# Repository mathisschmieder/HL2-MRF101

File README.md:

100W Amplifier Companion for the Hermes-Lite 2.x
================================================

See the [Wiki](https://github.com/mathisschmieder/HL2-MRF101/wiki) for details.

This is a work in progress to create a 100W power amplifier companion board for the [Hermes-Lite 2.x](http://www.hermeslite.com) using the NXP MRF101 MOSFET. It is based on WA2EUJ's [Single NXP MRF-101 Eval Board](https://sites.google.com/site/rfpowertools/) that won 1st place in the NXP Design Challenge.

First builds of revision 0.2 are successful. Several changes and additions were done by M5EVT to revision 0.3 and boards of that revision are currently being built and tested. See the Wiki for further links and details.

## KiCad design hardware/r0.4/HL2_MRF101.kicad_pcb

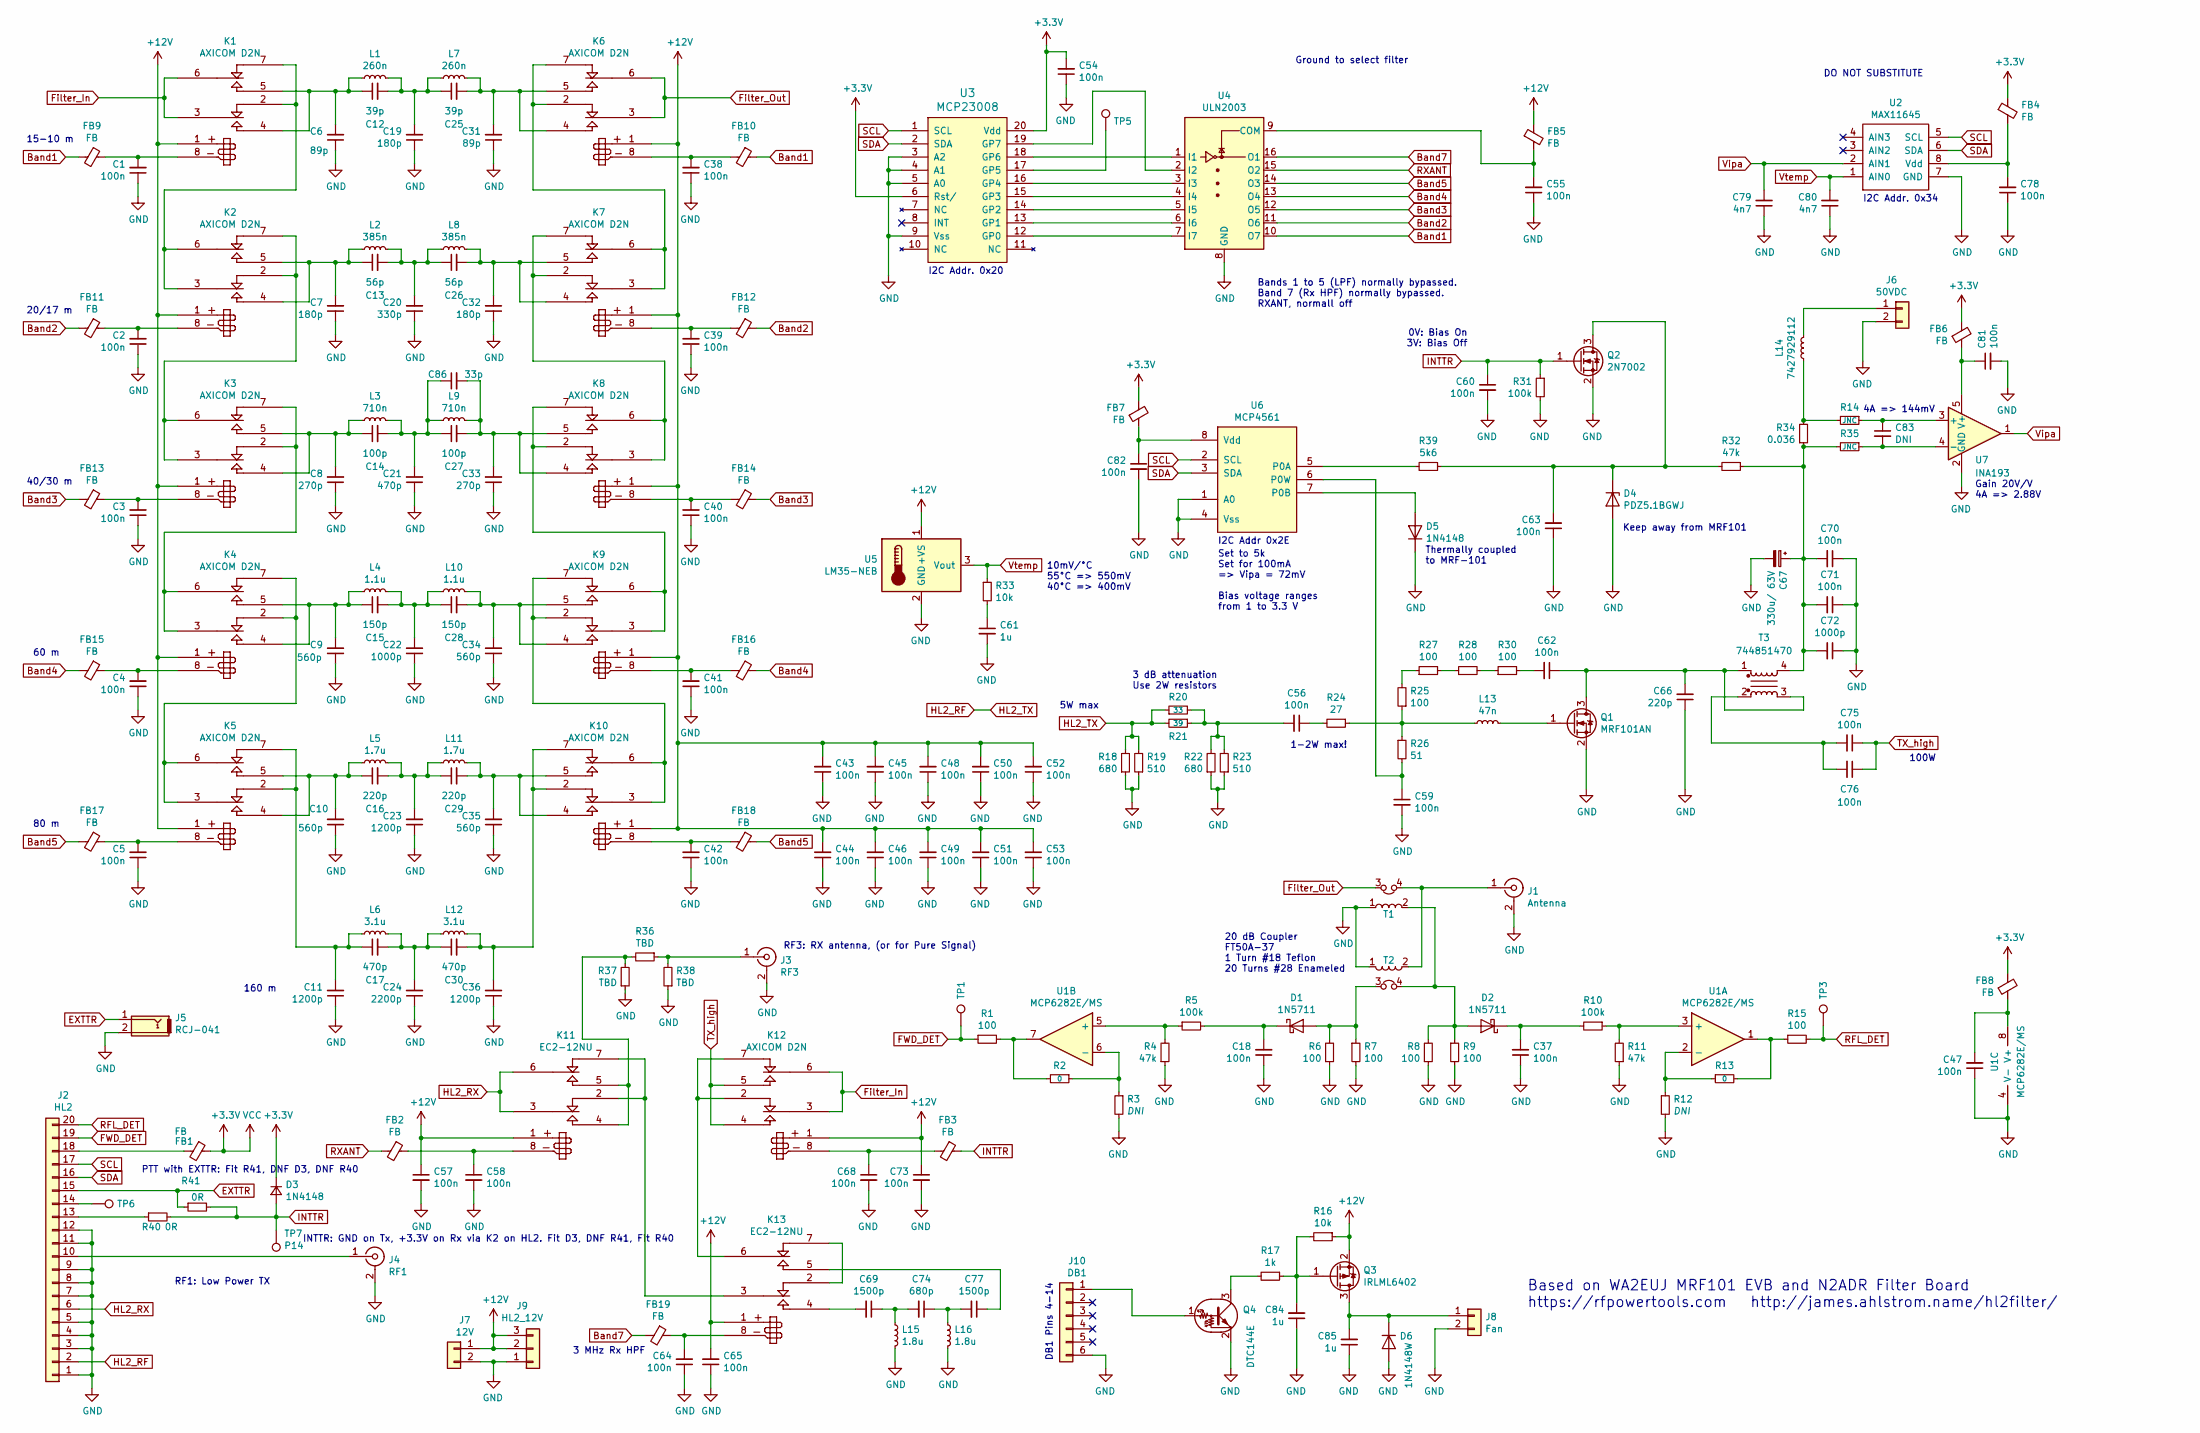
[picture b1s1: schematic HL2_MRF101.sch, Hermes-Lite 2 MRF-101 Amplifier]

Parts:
C1, C2, C3, C4, C5, C18, C37, C38, C39, C40, C41, C42, C43, C44, C45, C46, C47, C48, C49, C50, C51, C52, C53, C54, C55, C56, C57, C58, C59, C60, C62, C63, C64, C65, C68, C70, C71, C73, C75, C76, C78, C81, C82: 100n; C_0805_2012Metric
C6, C31: 89p; C_1206_3216Metric
C7, C19, C32: 180p; C_1206_3216Metric
C8, C33: 270p; C_1206_3216Metric
C9, C10, C34, C35: 560p; C_1206_3216Metric
C11, C23, C36: 1200p; C_1206_3216Metric
C12, C25: 39p; C_1206_3216Metric
C13, C26: 56p; C_1206_3216Metric
C14, C27: 100p; C_1206_3216Metric
C15, C28: 150p; C_1206_3216Metric
C16, C29: 220p; C_1206_3216Metric
C17, C21, C30: 470p; C_1206_3216Metric
C20: 330p; C_1206_3216Metric
C22: 1000p; C_1206_3216Metric
C24: 2200p; C_1206_3216Metric
C61, C84, C85: 1u; C_0805_2012Metric
C66: 220p; C_0805_2012Metric
C67: 330u/ 63V; CP_Radial_D10.0mm_P5.00mm
C69, C77: 1500p; C_0805_2012Metric
C72: 1000p; C_0805_2012Metric
C74: 680p; C_0805_2012Metric
C79, C80: 4n7; C_0805_2012Metric
C83: DNI; C_0805_2012Metric
C86: 33p; C_1206_3216Metric
D1, D2: 1N5711; D_SOD-123
D3: 1N4148; D_SOD-123
D4: PDZ5.1BGWJ; D_SOD-123
D5: 1N4148; D_DO-35_SOD27_P2.54mm_Vertical_KathodeUp
D6: 1N4148W; D_SOD-123
FB1, FB2, FB3, FB4, FB5, FB6, FB7, FB8, FB9, FB10, FB11, FB12, FB13, FB14, FB15, FB16, FB17, FB18, FB19: FB; L_0805_2012Metric
J1: Antenna; BNC_Amphenol_B6252HB-NPP3G-50_Horizontal
J2: HL2; PinSocket_1x20_P2.54mm_Vertical
J3: RF3; U.FL_Hirose_U.FL-R-SMT-1_Vertical
J4: RF1; U.FL_Hirose_U.FL-R-SMT-1_Vertical
J5: RCJ-041; PhonoRcaRCJ-04x
J6: 50VDC; TerminalBlock_Phoenix_PT-1,5-2-5.0-H_1x02_P5.00mm_Horizontal
J7: 12V; TerminalBlock_Phoenix_PT-1,5-2-3.5-H_1x02_P3.50mm_Horizontal
J8: Fan; JST_XH_B2B-XH-A_1x02_P2.50mm_Vertical
J9: HL2_12V; PinSocket_1x03_P2.54mm_Vertical
J10: DB1; PinHeader_1x06_P2.54mm_Vertical
K1, K2, K3, K4, K5, K6, K7, K8, K9, K10, K12: AXICOM D2N; RelayDPDT02
K11, K13: EC2-12NU; RelayDPDT01
L1, L7: 260n; T50_V_THT
L2, L8: 385n; T50_V_THT
L3, L9: 710n; T50_V_THT
L4, L10: 1.1u; T50_V_THT
L5, L11: 1.7u; T50_V_THT
L6, L12: 3.1u; T50_V_THT
L13: 47n; L_0805_2012Metric
L14: 7427929112; SignalCommunications-WE-PF_7427929XXX
L15, L16: 1.8u; L_1812_4532Metric
Q1: MRF101AN; TO-220-3_Vertical
Q2: 2N7002; SOT-23
Q3: IRLML6402; SOT-23
Q4: DTC144E; SOT-23
R1, R15: 100; R_0805_2012Metric
R2, R13: 0; R_0805_2012Metric
R3, R12: DNI; R_0805_2012Metric
R4, R11, R32: 47k; R_0805_2012Metric
R5, R10, R31: 100k; R_0805_2012Metric
R6, R7, R8, R9, R25, R27, R28, R30: 100; R_2512_6332Metric
R14, R35: JNC; R_0805_2012Metric
R16, R33: 10k; R_0805_2012Metric
R17: 1k; R_0805_2012Metric
R18, R22: 680; R_2512_6332Metric
R19, R23: 510; R_2512_6332Metric
R20: 33; R_2512_6332Metric
R21: 39; R_2512_6332Metric
R24: 27; R_2512_6332Metric
R26: 51; R_2512_6332Metric
R34: 0.036; R_0612_1632Metric
R36, R37, R38: TBD; R_0805_2012Metric
R39: 5k6; R_0805_2012Metric
R40, R41: 0R; R_0603_1608Metric
T1, T2: Coupler; T50_Coupler
T3: 744851470; SignalCommunications-WE-DCT
TP1, TP3, TP5, TP6: P8; TestPoint_Pad_D1.5mm
TP7: P14; TestPoint_Pad_D1.5mm
U1: MCP6282E/MS; MSOP-8_3x3mm_P0.65mm
U2: MAX11645; MAX11613
U3: MCP23008; SSOP-20_5.3x7.2mm_P0.65mm
U4: ULN2003; TSSOP-16_4.4x5mm_P0.65mm
U5: LM35-NEB; TO-220-3_Vertical
U6: MCP4561; MSOP-8_3x3mm_P0.65mm
U7: INA193; SOT-23-5

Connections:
+3V3: C54.2, D3.1 (K), FB1.1, FB4.1, FB6.2, FB7.2, FB8.2, U3.6 (Rst/), U3.20 (Vdd)
+12V: C43.2, C44.2, C45.2, C46.2, C48.2, C49.2, C50.2, C51.2, C52.2, C53.2, C57.1, C65.2, C73.1, FB5.1, J7.1, J9.2, J9.3, K1.1, K2.1, K3.1, K4.1, K5.1, K6.1, K7.1, K8.1, K9.1, K10.1, K11.1, K12.1, K13.1, Q3.2 (S), R16.1, U5.1 (+VS)
Band1: FB9.2, FB10.1, U4.10 (O7)
Band2: FB11.2, FB12.1, U4.11 (O6)
Band3: FB13.2, FB14.1, U4.12 (O5)
Band4: FB15.2, FB16.1, U4.13 (O4)
Band5: FB17.2, FB18.1, U4.14 (O3)
Band7: FB19.2, U4.16 (O1)
EXTTR: J2.15, J5.1, R41.1
FWD_DET: J2.19, R1.1, TP1.1
Filter_In: K1.3, K1.6, K12.3, K12.6
Filter_Out: K6.3, K6.6, T1.3
GND: C1.1, C2.1, C3.1, C4.1, C5.1, C6.1, C7.1, C8.1, C9.1, C10.1, C11.1, C18.1, C19.1, C20.1, C21.1, C22.1, C23.1, C24.1, C31.1, C32.1, C33.1, C34.1, C35.1, C36.1, C37.1, C38.1, C39.1, C40.1, C41.1, C42.1, C43.1, C44.1, C45.1, C46.1, C47.1, C48.1, C49.1, C50.1, C51.1, C52.1, C53.1, C54.1, C55.1, C57.2, C58.2, C59.2, C60.2, C61.2, C63.1, C64.1, C65.1, C66.1, C67.2, C68.2, C70.1, C71.1, C72.1, C73.2, C78.1, C79.1, C80.1, C81.2, C82.2, C84.1, C85.1, D4.2 (A), D5.1 (K), D6.2 (A), J1.2 (Ext), J2.1, J2.3, J2.4, J2.5, J2.7, J2.8, J2.9, J2.11, J2.12, J3.2 (Ext), J4.2 (Ext), J5.2, J6.2, J7.2, J8.2, J9.1, J10.6, L15.2, L16.2, Q1.2 (S), Q2.2 (S), Q4.2 (E), R3.2, R4.1, R6.1, R7.2, R8.1, R9.2, R11.1, R12.2, R18.1, R19.1, R22.1, R23.1, R31.2, R37.1, R38.1, T1.1, T2.1, U1.4 (V-), U2.7 (GND), U3.3 (A2), U3.4 (A1), U3.5 (A0), U3.9 (Vss), U4.8 (GND), U5.2 (GND), U6.1 (A0), U6.4 (Vss), U7.2 (GND); also elsewhere on the board
HL2_RF: J2.2, R18.2, R19.2, R20.1, R21.2
HL2_RX: J2.6, K11.3, K11.6
INTTR: C60.1, D3.2 (A), FB3.1, Q2.1 (G), R31.1, R40.2, R41.2, TP7.1
unnamed: C1.2, FB9.1, K1.8
unnamed: C2.2, FB11.1, K2.8
unnamed: C3.2, FB13.1, K3.8
unnamed: C4.2, FB15.1, K4.8
unnamed: C5.2, FB17.1, K5.8
unnamed: C10.2, C16.1, K5.4, K5.5, L5.1
unnamed: C11.2, C17.1, K5.2, K5.7, L6.1
unnamed: C6.2, C12.1, K1.4, K1.5, L1.1
unnamed: C12.2, C19.2, C25.1, L1.2, L7.1
unnamed: C7.2, C13.1, K2.4, K2.5, L2.1
unnamed: C13.2, C20.2, C26.1, L2.2, L8.1
unnamed: C8.2, C14.1, K3.4, K3.5, L3.1
unnamed: C14.2, C21.2, C27.1, C86.1, L3.2, L9.1
unnamed: C9.2, C15.1, K4.4, K4.5, L4.1
unnamed: C15.2, C22.2, C28.1, L4.2, L10.1
unnamed: C16.2, C23.2, C29.1, L5.2, L11.1
unnamed: C17.2, C24.2, C30.1, L6.2, L12.1
unnamed: C18.2, D1.1 (K), R5.2
unnamed: C25.2, C31.2, K6.4, K6.5, L7.2
unnamed: C26.2, C32.2, K7.4, K7.5, L8.2
unnamed: C27.2, C33.2, C86.2, K8.4, K8.5, L9.2
unnamed: C28.2, C34.2, K9.4, K9.5, L10.2
unnamed: C29.2, C35.2, K10.4, K10.5, L11.2
unnamed: C30.2, C36.2, K10.2, K10.7, L12.2
unnamed: C37.2, D2.1 (K), R10.2
unnamed: C38.2, FB10.2, K6.8
unnamed: C39.2, FB12.2, K7.8
unnamed: C40.2, FB14.2, K8.8
unnamed: C41.2, FB16.2, K9.8
unnamed: C42.2, FB18.2, K10.8
unnamed: C47.2, FB8.1, U1.8 (V+)
unnamed: C55.2, FB5.2, U4.9 (COM)
unnamed: C56.1, R24.2
unnamed: C56.2, R20.2, R21.1, R22.2, R23.2
unnamed: C58.1, FB2.1, K11.8
unnamed: C59.1, R26.2, U6.6 (P0W)
unnamed: C61.1, R33.2
unnamed: C62.1, C66.2, Q1.3 (D), T3.1, T3.3
unnamed: C62.2, R30.2
unnamed: C63.2, D4.1 (K), Q2.3 (D), R32.2, R39.1
unnamed: C64.2, FB19.1, K13.8
unnamed: C67.1, C70.2, C71.2, C72.2, R32.1, R34.1, R35.2, T3.4
unnamed: C68.1, FB3.2, K12.8
unnamed: C69.1, C74.2, L15.1
unnamed: C69.2, K13.4
unnamed: C74.1, C77.2, L16.1
unnamed: C75.2, C76.2, T3.2
unnamed: C77.1, K13.5
unnamed: C78.2, FB4.2, U2.8 (Vdd)
unnamed: C81.1, FB6.1, U7.5 (V+)
unnamed: C82.1, FB7.1, U6.8 (Vdd)
unnamed: C83.1, R14.1, U7.3 (+)
unnamed: C83.2, R35.1, U7.4 (-)
unnamed: C84.2, Q3.1 (G), R16.2, R17.1
unnamed: C85.2, D6.1 (K), J8.1, Q3.3 (D)
unnamed: D1.2 (A), R6.2, R7.1, T2.3
unnamed: D2.2 (A), R8.2, R9.1, T1.2, T2.4
unnamed: D5.2 (A), U6.7 (P0B)
unnamed: FB1.2, J2.18
unnamed: J1.1 (In), T1.4, T2.2
unnamed: J2.10, J4.1 (In)
unnamed: J2.13, R40.1
unnamed: J2.14, TP6.1
unnamed: J3.1 (In), R36.1, R38.2
unnamed: J6.1, L14.1
unnamed: J10.1, Q4.1 (B)
unnamed: K1.2, K1.7, K2.3, K2.6
unnamed: K2.2, K2.7, K3.3, K3.6
unnamed: K3.2, K3.7, K4.3, K4.6
unnamed: K4.2, K4.7, K5.3, K5.6
unnamed: K6.2, K6.7, K7.3, K7.6
unnamed: K7.2, K7.7, K8.3, K8.6
unnamed: K8.2, K8.7, K9.3, K9.6
unnamed: K9.2, K9.7, K10.3, K10.6
unnamed: K11.2, K11.7, K13.3
unnamed: K11.4, K11.5, R36.2, R37.2
unnamed: K12.2, K12.7, K13.6
unnamed: K13.2, K13.7
unnamed: L13.1, R24.1, R25.1, R26.1
unnamed: L13.2, Q1.1 (G)
unnamed: L14.2, R14.2, R34.2
unnamed: Q4.3 (C), R17.2
unnamed: R1.2, R2.2, U1.7
unnamed: R2.1, R3.1, U1.6 (-)
unnamed: R4.2, R5.1, U1.5 (+)
unnamed: R10.1, R11.2, U1.3 (+)
unnamed: R12.1, R13.1, U1.2 (-)
unnamed: R13.2, R15.1, U1.1
unnamed: R25.2, R27.1
unnamed: R27.2, R28.1
unnamed: R28.2, R30.1
unnamed: R39.2, U6.5 (P0A)
unnamed: TP5.1, U3.17 (GP5)
unnamed: U3.12 (GP0), U4.7 (I7)
unnamed: U3.13 (GP1), U4.6 (I6)
unnamed: U3.14 (GP2), U4.5 (I5)
unnamed: U3.15 (GP3), U4.4 (I4)
unnamed: U3.16 (GP4), U4.3 (I3)
unnamed: U3.18 (GP6), U4.1 (I1)
unnamed: U3.19 (GP7), U4.2 (I2)
RFL_DET: J2.20, R15.2, TP3.1
RXANT: FB2.2, U4.15 (O2)
SCL: J2.17, U2.5 (SCL), U3.1 (SCL), U6.2 (SCL)
SDA: J2.16, U2.6 (SDA), U3.2 (SDA), U6.3 (SDA)
TX_high: C75.1, C76.1, K12.4, K12.5
Vipa: C79.2, U2.2 (AIN1), U7.1
Vtemp: C80.2, R33.1, U2.1 (AIN0), U5.3 (Vout)

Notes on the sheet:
0V: Bias On 3V: Bias Off
Thermally coupled to MRF-101
Set to 5k Set for 100mA => Vipa = 72mV Bias voltage ranges from 1 to 3.3 V
1-2W max!
100W
Based on WA2EUJ MRF101 EVB and N2ADR Filter Board https://rfpowertools.com http://james.ahlstrom.name/hl2filter/
3 dB attenuation Use 2W resistors
20 dB Coupler FT50A-37 1 Turn #18 Teflon 20 Turns #28 Enameled
3 MHz Rx HPF
15-10 m
20/17 m
40/30 m
60 m
80 m
160 m
Bands 1 to 5 (LPF) normally bypassed. Band 7 (Rx HPF) normally bypassed. RXANT, normall off
Ground to select filter
5W max
RF1: Low Power TX
INTTR: GND on Tx, +3.3V on Rx via K2 on HL2. Fit D3, DNF R41, Fit R40
10mV/°C 55°C => 550mV 40°C => 400mV
I2C Addr. 0x20
I2C Addr. 0x34
I2C Addr 0x2E
4A => 144mV
Gain 20V/V 4A => 2.88V
DB1 Pins 4-14
PTT with EXTTR: Fit R41, DNF D3, DNF R40
RF3: RX antenna, (or for Pure Signal)
DO NOT SUBSTITUTE
Keep away from MRF101

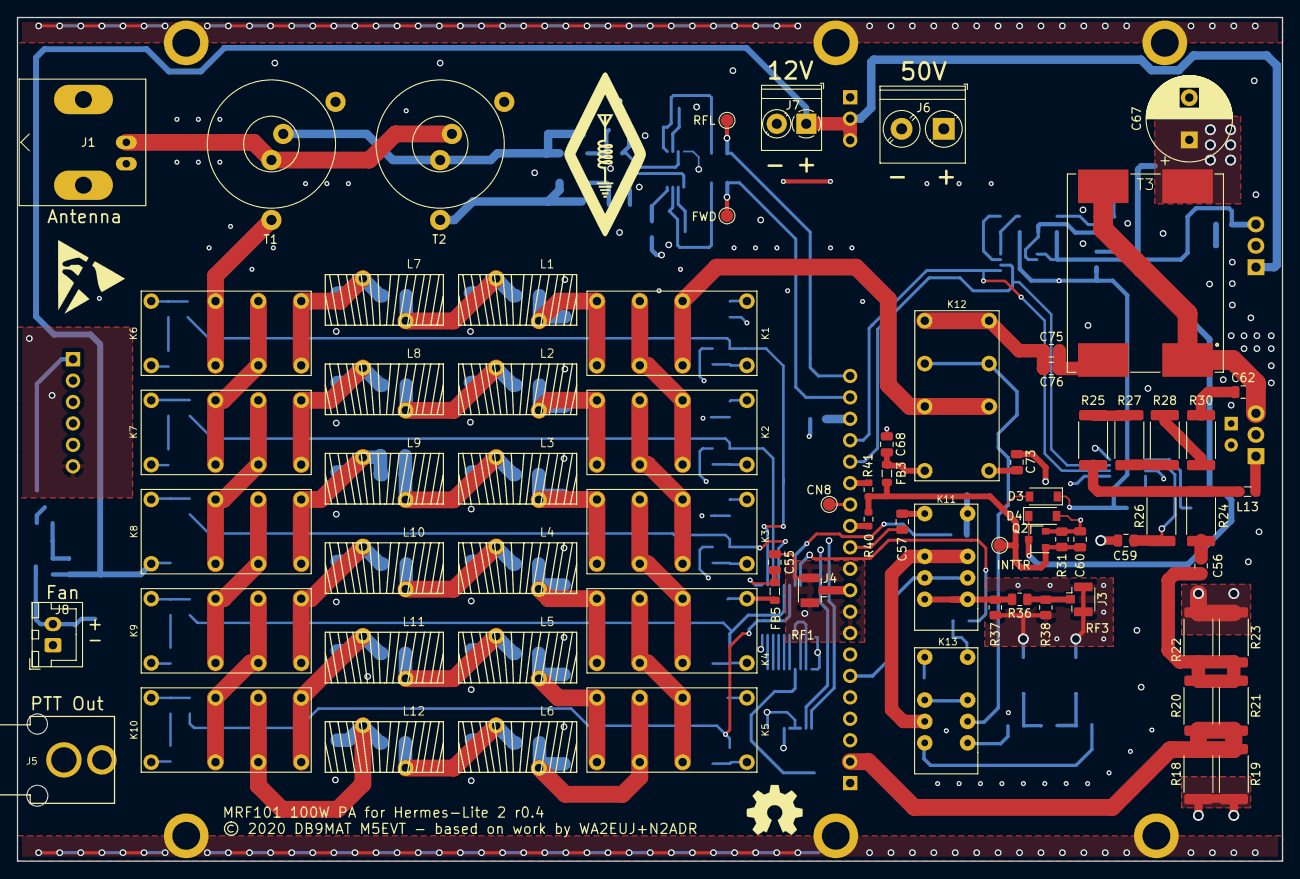
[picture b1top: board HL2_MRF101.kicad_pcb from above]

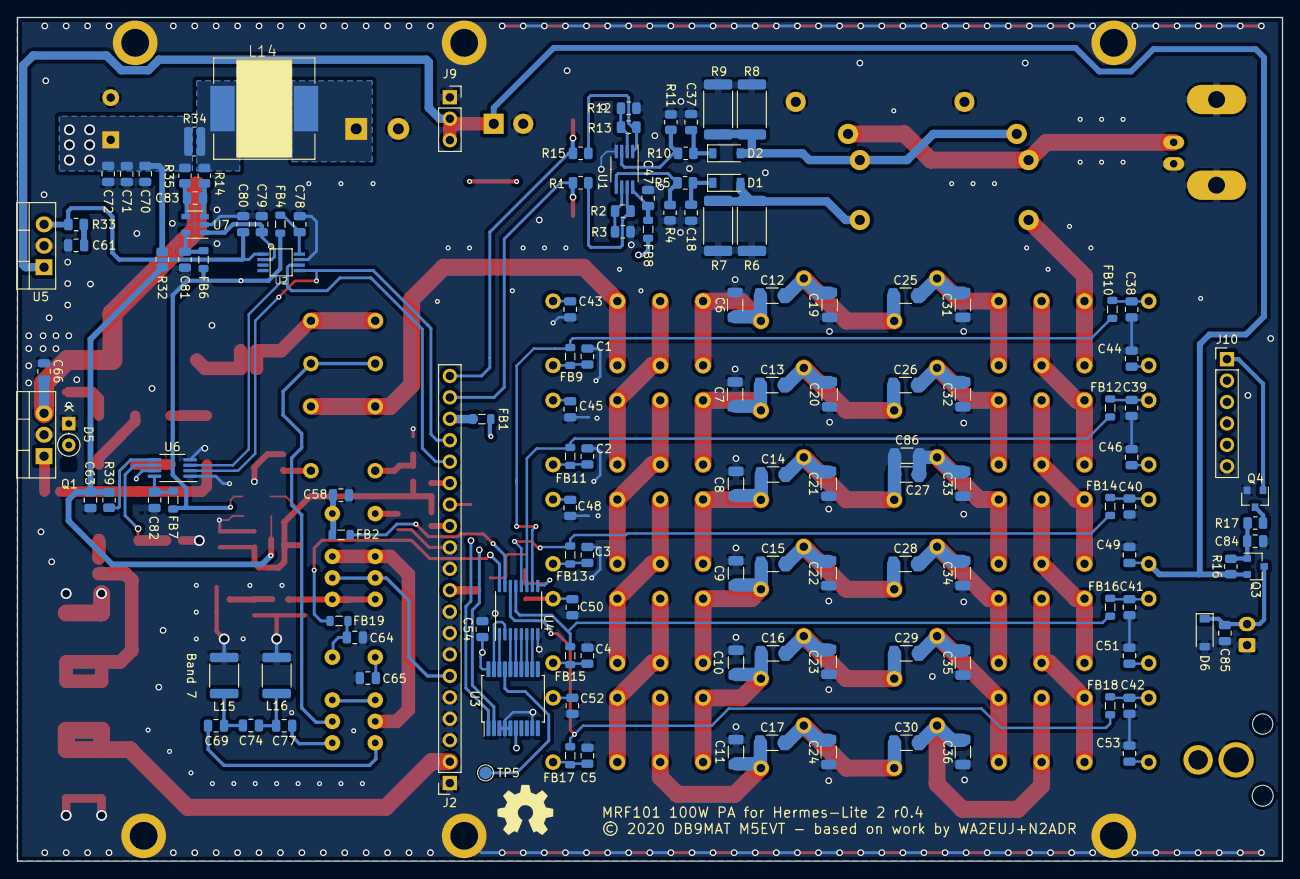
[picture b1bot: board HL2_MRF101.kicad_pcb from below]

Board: 4 copper layers, 149.9 x 100.0 mm, 215 parts (135 on the bottom side), 123 nets.

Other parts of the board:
MH: VAL**; m3
MH#2, MH#3, MH#4, MH#5, MH#6: VAL**; m3

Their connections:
GND: MH.1, MH#2.1, MH#3.1, MH#4.1, MH#5.1, MH#6.1; also elsewhere on the board

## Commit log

2020-01-01 Initial commit
    Initial commit of schematics
2020-01-03 Updated schematics; added footprints
2020-01-03 Updated schematics PDF
2020-01-05 Components layed out
2020-01-05 Updated component layout
2020-01-05 Wiring started
2020-01-12 Revision 0.1 finished
2020-01-12 Relocated C47
2020-01-12 Updated R6-9 to 1206 1/2W
2020-01-12 Updated one trace width
2020-01-12 Reworked Op Amps
2020-01-13 Updated layout
2020-01-13 Started adding current monitor
2020-01-14 Added bias control and current monitor
2020-01-14 Started current monitor layout
2020-01-14 Further routing
2020-01-27 Added ferrites, fan control
    Added ferrite beads to relays
    Added PWM fan control via DB1 on HL2
2020-01-27 Reworked bias circuit
2020-01-30 Reworked bias circuit, again.
2020-02-20 Gerbers for first ordered prototype
2020-02-20 Impedance Adjustment started
2020-02-21 Almost finished reworking FET part
2020-02-21 Updated FET circuit
2020-02-22 Revision 0.2
2020-06-06 Rx antenna change
    RX antenna routed through HL2 rx antenna connection. High power tx tracks thickened to 2 mm and net list added for 50 ohm impedance top and bottom tracks for clearance.
2020-07-03 Update relays
2020-07-03 filter_measurements
2020-09-05 Cleaned up silk screen
2020-09-05 Cleaned up repository
2020-09-05 Added Readme.
2021-07-03 Issue fixing (#9 #8 #5 #4 #3 #2), fixing library paths, schematic and pcb changed, up-issued to r4

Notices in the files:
hardware/r0.4/HL2_MRF101.kicad_pcb:
© 2020 DB9MAT M5EVT - based on work by WA2EUJ+N2ADR
